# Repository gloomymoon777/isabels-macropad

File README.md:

# isabel's macropad

Hello, Isabel here!! this is my first submission for blueprint. I followed the hackpad tutorial and added more features and some minor design changes; specifically, my hackpad has 8 keys, 3 neopixels, and one knob. I also used qmk firmware to make the keys work!

# PCB

I originally tried adding the switches individually, but I ran out of pins, so I decided to use a matrix instead: 

This was my first time using KiCad, and I think it took me around 5 hours just to figure everything out.. but it's okay because at least I was able to learn something new!

It looks like a big mess (it is) but I guess it's to be expected from a beginner. Routing the PCB was pretty fun regardless though!!
I also wasn't sure why I couldn't get 3D images to show on my PCB design, but if it works it works yk.

# CAD

This part was actually pretty straightforward, since I have used Fusion360 before! 
I still spent a decent amount of time on it just to make sure everything fit with the PCB though.

# Firmware
I followed some qmk tutorials for this part! 
Honestly I was really confused for all of this and the code may not work, but I will fix that if and/or when the project gets shipped :D

# Thoughts
Making this was really fun but really frustrating, especially in the beginning. KiCad has such a big learning curve, especially without a guide. If I could do this again, I would definitely take a look at the hackpad resources on blueprint first (I unfortunately didn't see it when I started). However, I was able to explore on my own and learn how to design a PCB + build a mini keyboard! yay!!

# BOM 
- 1 SEEEDUINO XIAO RP2040: $3.99 (https://www.seeedstudio.com/Seeeduino-XIAO-Arduino-Microcontroller-SAMD21-Cortex-M0+-p-4426.html?srsltid=AfmBOorT96zUK38616pjHdfXnMnU0o0y1qJc7lplFwdJuFrqgMMRAf41)
- 1 EC11 Encoder $1.45 (https://tinkersphere.com/electronic-components/1326-rotary-encoder-ec11.html?srsltid=AfmBOopOo-vrdPzgLJg3iHv4EmU_9wukVdqNCnXfHaQcgdfFJyrRNw5Z5jo)
- 8 Cherry MX switches $0.32 each, $2.56 total (https://mechanicalkeyboards.com/products/cherry-mx-speed-silver-45g-linear?variant=47607468425516)
- 8 Cherry MX keycaps $5.95, 10 pack (https://www.adafruit.com/product/4998)
- 8 1N4148 Diodes $0.74 each, $5.92 total (https://www.mouser.com/ProductDetail/Microchip-Technology/1N4148-1?qs=%252BRKXB2WKlSdJR%252BwP8jtUHQ%3D%3D&mgh=1&srsltid=AfmBOooron7OYLItBWxreR001qZg3yBlkAta0VMUpKXsrnzb_KWjFGqUDeA)
- 3 SK6812 neopixel LEDs $3.95, 10 pack (https://www.adafruit.com/product/4892?srsltid=AfmBOooCAh1CvULMOHKEZYruWb9CKOdRJAxNbOx5X2afPDqtHWVynWcv)
- PCB ~27 dollars pcbway
- 4 screws (same as ones on tutorial) --> 4x M3x16 Bolt: 0.80 set of 10 (https://www.dfrobot.com/product-845.html?srsltid=AfmBOorcYq0fSDSSL-BlJ3uggQFwOURX8cUfa63UACWloX7z5vpRYJ0uUMs)

Total: $51.62

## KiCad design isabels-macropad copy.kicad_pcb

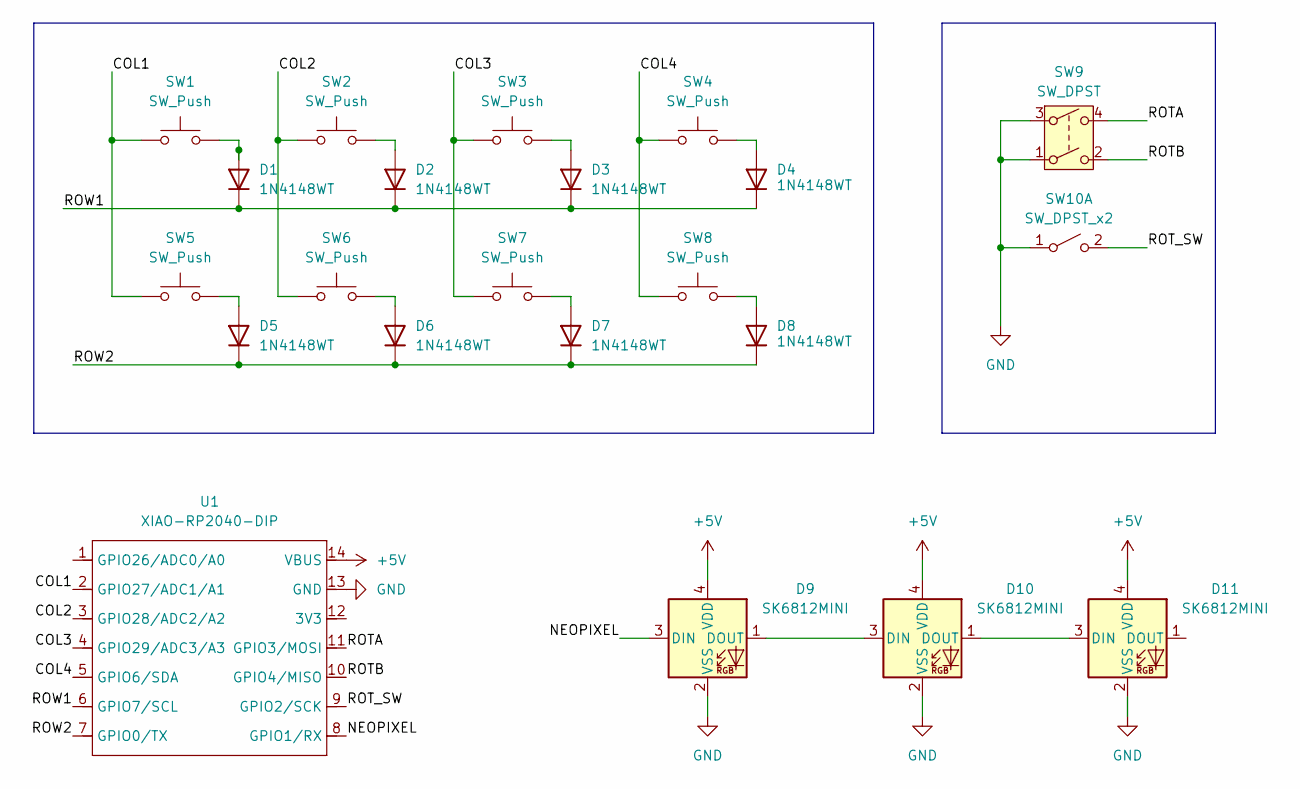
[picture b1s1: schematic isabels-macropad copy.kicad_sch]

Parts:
D1, D2, D3, D4, D5, D6, D7, D8: 1N4148WT; D_SOD-523
D9, D10, D11: SK6812MINI; LED_SK6812MINI_PLCC4_3.5x3.5mm_P1.75mm
SW1, SW2, SW3, SW4, SW5, SW6, SW7, SW8: SW_Push; SW_Cherry_MX_1.00u_PCB
SW9: SW_DPST; RotaryEncoder_Alps_EC11E-Switch_Vertical_H20mm_CircularMoun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
SW10: SW_DPST_x2; RotaryEncoder_Alps_EC11E-Switch_Vertical_H20mm_CircularMoun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
U1: XIAO-RP2040-DIP

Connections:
+5V: D9.4 (VDD), D10.4 (VDD), D11.4 (VDD), U1.14 (VBUS)
/COL1: SW1.1, SW5.1, U1.2 (GPIO27/ADC1/A1)
/COL2: SW2.1, SW6.1, U1.3 (GPIO28/ADC2/A2)
/COL3: SW3.1, SW7.1, U1.4 (GPIO29/ADC3/A3)
/COL4: SW4.1, SW8.1, U1.5 (GPIO6/SDA)
/NEOPIXEL: D9.3 (DIN), U1.8 (GPIO1/RX)
/ROTA: SW9.4, U1.11 (GPIO3/MOSI); also elsewhere on the board
/ROTB: SW9.2, U1.10 (GPIO4/MISO); also elsewhere on the board
/ROT_SW: SW10.2 (B), U1.9 (GPIO2/SCK); also elsewhere on the board
/ROW1: D1.1 (K), D2.1 (K), D3.1 (K), D4.1 (K), U1.6 (GPIO7/SCL)
/ROW2: D5.1 (K), D6.1 (K), D7.1 (K), D8.1 (K), U1.7 (GPIO0/TX)
GND: D9.2 (VSS), D10.2 (VSS), D11.2 (VSS), SW9.1, SW9.3, SW10.1 (A), U1.13 (GND); also elsewhere on the board
unnamed: D1.2 (A), SW1.2
unnamed: D2.2 (A), SW2.2
unnamed: D3.2 (A), SW3.2
unnamed: D4.2 (A), SW4.2
unnamed: D5.2 (A), SW5.2
unnamed: D6.2 (A), SW6.2
unnamed: D7.2 (A), SW7.2
unnamed: D8.2 (A), SW8.2
unnamed: D9.1 (DOUT), D10.3 (DIN)
unnamed: D10.1 (DOUT), D11.3 (DIN)

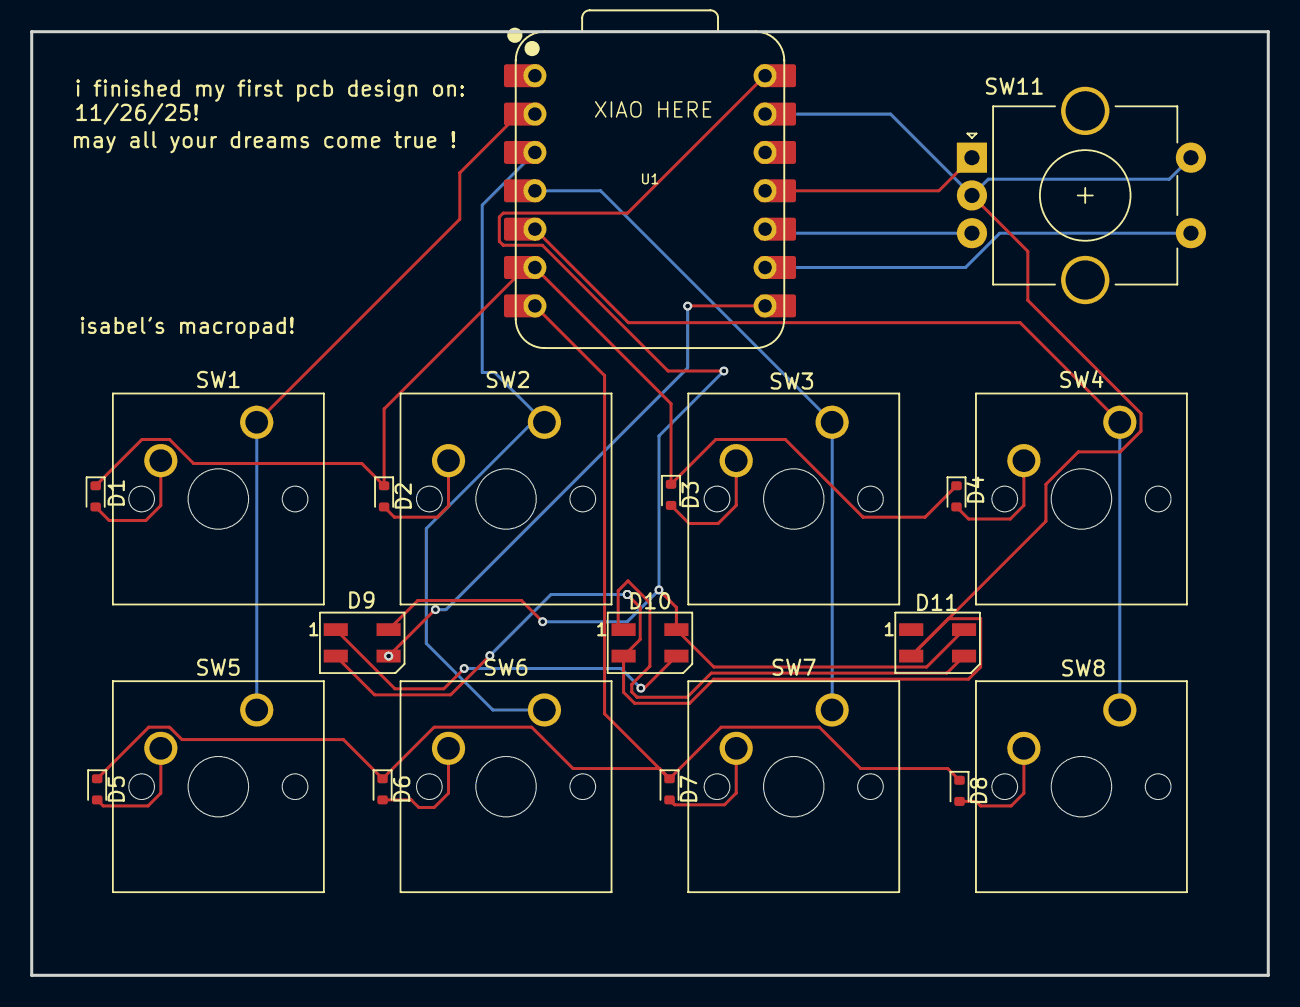
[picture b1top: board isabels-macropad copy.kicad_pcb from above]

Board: 2 copper layers, 81.9 x 62.5 mm, 21 parts (0 on the bottom side), 22 nets.

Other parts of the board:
SW11: RotaryEncoder_Switch; RotaryEncoder_Alps_EC11E-Switch_Vertical_H20mm_CircularMoun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

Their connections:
/ROTA: SW11.A; also elsewhere on the board
/ROTB: SW11.B; also elsewhere on the board
/ROT_SW: SW11.S1; also elsewhere on the board
GND: SW11.C, SW11.S2; also elsewhere on the board

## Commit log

2025-11-27 added files
2025-11-27 README
    Expanded the README to include detailed project information, PCB design process, CAD design insights, firmware development experience, and a bill of materials.
2025-11-29 README
2025-11-29 Clean up formatting
2025-11-29 put files into folders
2025-11-29 updated BOM
    Updated BOM with prices and links for components.
2025-11-30 testing
2025-11-30 Add new components to BOM.csv
2025-11-30 Add empty fields to PCB entry in BOM.csv
2025-11-30 Fix BOM.csv formatting
2025-11-30 Update BOM.csv with total cost calculation
2025-11-30 remove file no needed
2025-11-30 updated steps
2025-11-30 added better render
